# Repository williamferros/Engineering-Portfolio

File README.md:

# William Ferros Engineering Portfolio

## Publish with GitHub Pages

1. Delete the old contents of your `Engineering-Portfolio` repository, or upload these files over them.
2. Upload **the contents of this folder**, not the outer `william-ferros-portfolio` folder.
3. Confirm that `index.html` is visible at the repository root.
4. Open **Settings → Pages**.
5. Choose **Deploy from a branch**.
6. Select `main` and `/(root)`, then save.
7. Your site will appear at:
   `https://williamferros.github.io/Engineering-Portfolio/`

The source files and reports are intentionally included so portfolio visitors can open or download them.

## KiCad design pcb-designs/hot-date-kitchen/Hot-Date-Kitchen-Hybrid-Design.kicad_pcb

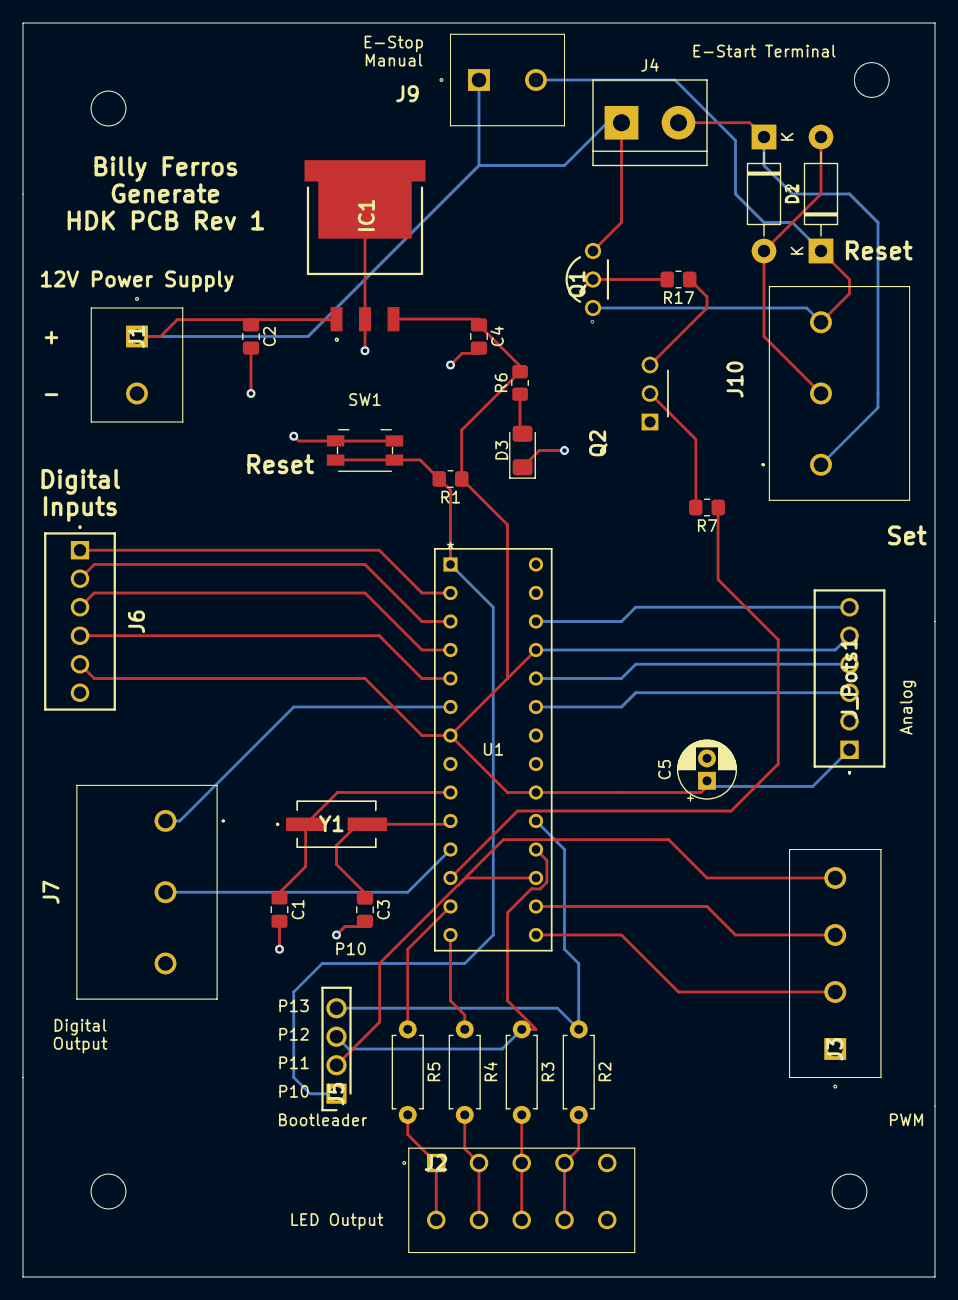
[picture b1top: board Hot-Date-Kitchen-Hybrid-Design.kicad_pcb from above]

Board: 2 copper layers, 81.3 x 111.8 mm, 32 parts (0 on the bottom side), 35 nets.

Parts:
C1, C3: 26pF; C_0805_2012Metric_Pad1.18x1.45mm_HandSolder
C2: 0.33uF; C_0805_2012Metric_Pad1.18x1.45mm_HandSolder
C4: 0.1uF; C_0805_2012Metric_Pad1.18x1.45mm_HandSolder
C5: 10uF; CP_Radial_D5.0mm_P2.00mm
D1, D2: 1N4001; D_DO-41_SOD81_P10.16mm_Horizontal
D3: LED; LED_1206_3216Metric_Pad1.42x1.75mm_HandSolder
IC1: LM7805SX_NOPB; KTT0003B
J1: 12V Power Supply; 1729128
J2: LED Screw Terminal; 1705579
J3: Motor PWM Terminal; 1729144
J4: E-Start Terminal; TerminalBlock_bornier-2_P5.08mm
J5: Burn BootLeader Input; RHDR4W70P0X254_1X4_1056X250X865P
J6: Digital Inputs; 1725698
J7: Digital outputs; 1714968
J9: E-Stop Manual; 1729128
J10: Relay Control; 1714968
J_Pots1: Digital Inputs; 1725698
Q1: BC32740TA; 2N3906TA
Q2: 2N3904; TO254P508X877-3
R1, R7: 10K; R_0805_2012Metric_Pad1.20x1.40mm_HandSolder
R2, R3, R4, R5: 330; R_Axial_DIN0207_L6.3mm_D2.5mm_P7.62mm_Horizontal
R6: 220; R_0805_2012Metric_Pad1.20x1.40mm_HandSolder
R17: 1K; R_0805_2012Metric_Pad1.20x1.40mm_HandSolder
SW1: SW_Push; Panasonic_EVQPUJ_EVQPUA
U1: ATMega328p; CONN_110-43-328-41-001000_MIM
Y1: 16MHz; ABLS7M216000MHZD2YT

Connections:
+5V: C4.1, C5.1, IC1.3 (OUTPUT), J6.5, J_Pots1.1, R1.1, R6.2, U1.7 (Vcc), U1.20 (ARef)
+12V: C2.1, IC1.1 (INPUT), J1.1, J4.1, J9.1, Q1.3 (E)
/A0: J_Pots1.3, U1.23 (PC0)
/A1: J_Pots1.4, U1.24 (PC1)
/A2: J_Pots1.5, U1.25 (PC2)
/A3: J_Pots1.6, U1.26 (PC3)
/DI1: J6.1, U1.2 (PD0)
/DI2: J6.2, U1.3 (PD1)
/DI3: J6.3, U1.4 (PD2)
/DI4: J6.4, U1.5 (PD3)
/DO1: J7.1, U1.6 (PD4)
/DO2: J7.2, U1.11 (PD5)
/E-Stop: R7.1, U1.12 (PD6)
/LED1: R5.1, U1.13 (PD7)
/LED2: R4.1, U1.14 (PB0)
/LED3: J5.3, R3.1, U1.18 (PB4)
/LED4: J5.4, R2.1, U1.19 (PB5)
/PWM1: J3.2, U1.15 (PB1)
/PWM2: J3.3, U1.16 (PB2)
/PWM3: J3.4, J5.2, U1.17 (PB3)
/Pin10: J5.1, R1.2, SW1.2, U1.1 (PC6)
/Reset: D1.1 (K), J9.2, J10.3, Q1.1 (C)
/Set: D2.1 (K), J4.2, J10.1
GND: C1.2, C2.2, C3.2, C4.2, C5.2, D3.1 (K), IC1.2 (GND_1), IC1.4 (GND_2), IC1.6, J1.2, J2.9 (5.1), J2.10 (5.2), J3.1, J6.6, J7.3, J_Pots1.2, Q2.1 (E), SW1.1, U1.8 (GND), U1.22 (GND)
unnamed: C1.1, U1.9 (XTAL1), Y1.1
unnamed: C3.1, U1.10 (XTAL2), Y1.2
unnamed: D1.2 (A), D2.2 (A), J10.2
unnamed: D3.2 (A), R6.1
unnamed: J2.1 (1.1), J2.2 (1.2), R5.2
unnamed: J2.3 (2.1), J2.4 (2.2), R4.2
unnamed: J2.5 (3.1), J2.6 (3.2), R3.2
unnamed: J2.7 (4.1), J2.8 (4.2), R2.2
unnamed: Q2.2 (B), R7.2
unnamed: Q2.3 (C), R17.1
unnamed: Q1.2 (B), R17.2
